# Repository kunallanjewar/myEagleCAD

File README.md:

# myEagleCAD

My EagleCAD circuit design for HAB IoT project.
Visit: https://sites.google.com/a/asu.edu/iot/

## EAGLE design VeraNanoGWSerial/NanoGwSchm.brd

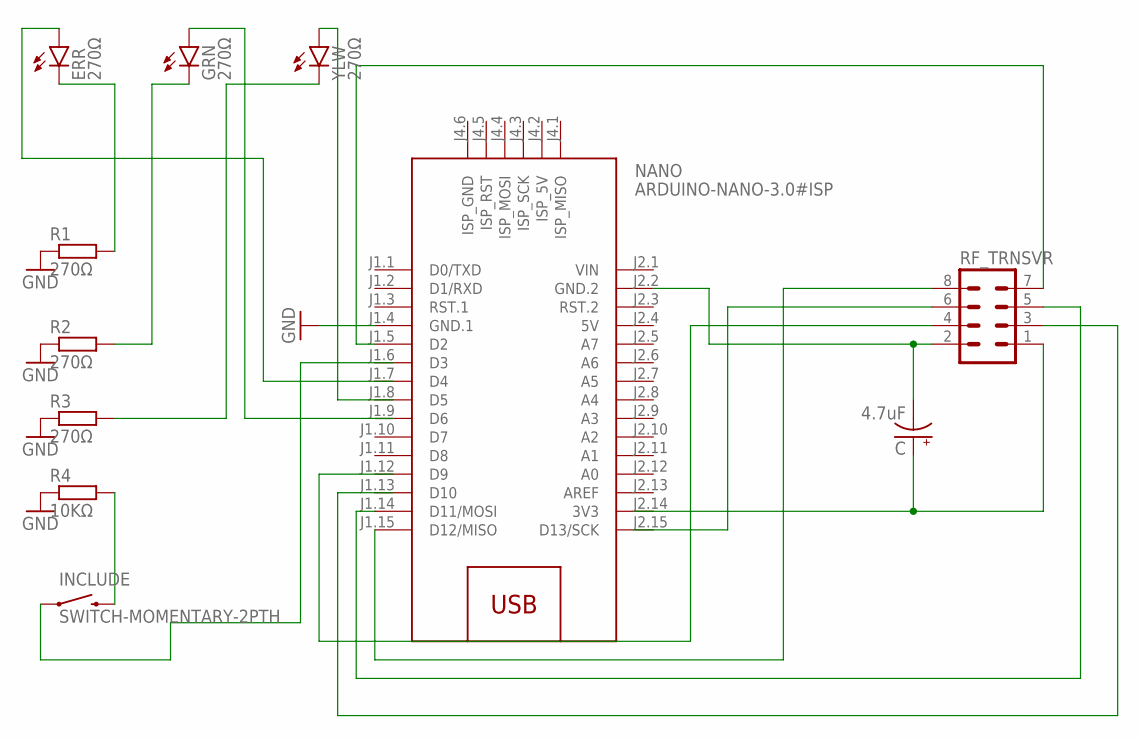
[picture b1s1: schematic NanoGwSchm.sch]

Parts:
C: 4.7uF; E2-5
ERR: 270Ω; LED5MM
GRN: 270Ω; LED5MM
INCLUDE: SWITCH-MOMENTARY-2PTH; TACTILE-PTH
NANO: ARDUINO-NANO-3.0#ISP
R1, R2, R3: 270Ω; 0204/7
R4: 10KΩ; 0204/7
RF_TRNSVR: MA04-2
YLW: 270Ω; LED5MM

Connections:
3V3: NANO.J2.14 (3V3)
5V: NANO.J2.4 (5V)
GND: NANO.J1.4 (GND.1), R1.1, R2.1, R3.1, R4.1
unnamed: ERR.K (C), R1.2
unnamed: GRN.K (C), R2.2
unnamed: R3.2, YLW.K (C)
unnamed: INCLUDE.3 (2), R4.2
unnamed: C.-, NANO.J2.2 (GND.2), RF_TRNSVR.2
unnamed: NANO.J1.14 (D11/MOSI), RF_TRNSVR.5
unnamed: NANO.J1.5 (D2), RF_TRNSVR.7
unnamed: NANO.J1.15 (D12/MISO), RF_TRNSVR.8
unnamed: C.+, RF_TRNSVR.1
VIN: NANO.J2.1 (VIN)

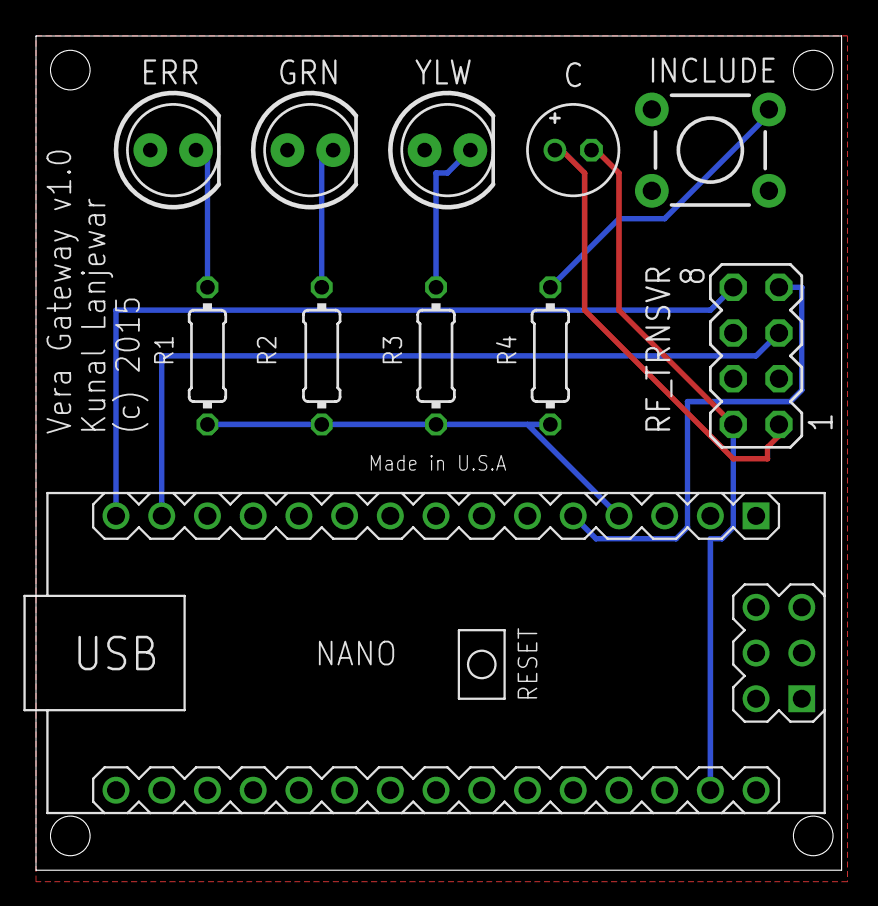
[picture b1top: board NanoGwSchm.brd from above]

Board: 2 copper layers, 44.8 x 46.3 mm, 11 parts (0 on the bottom side), 10 nets.

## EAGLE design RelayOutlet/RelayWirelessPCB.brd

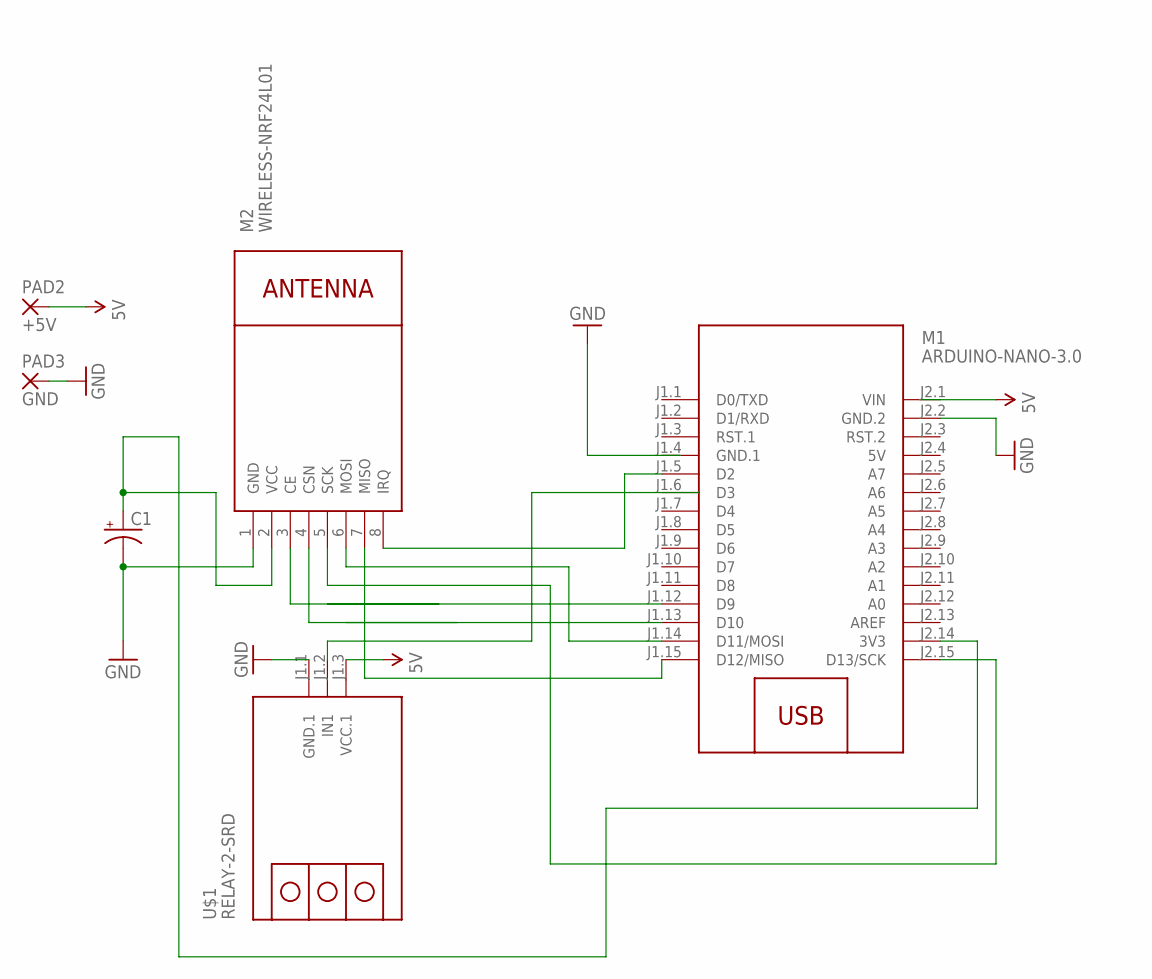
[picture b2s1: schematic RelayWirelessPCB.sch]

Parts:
C1: CPOL-USE3.5-8; E3,5-8
M1: ARDUINO-NANO-3.0
M2: WIRELESS-NRF24L01
PAD2: +5V; 4,16O1,6
PAD3: GND; 4,16O1,6
U$1: RELAY-2-SRD

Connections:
5V: M1.J2.1 (VIN), M1.J2.4 (5V), PAD2.1, U$1.J1.3 (VCC.1)
GND: C1.-, M1.J2.2 (GND.2), M2.1 (GND), PAD3.1, U$1.J1.1 (GND.1)
GND.1: M1.J1.4 (GND.1)
unnamed: M1.J1.12 (D9), M2.3 (CE)
unnamed: M1.J1.13 (D10), M2.4 (CSN)
unnamed: M1.J2.15 (D13/SCK), M2.5 (SCK)
unnamed: M1.J1.14 (D11/MOSI), M2.6 (MOSI)
unnamed: C1.+, M1.J2.14 (3V3), M2.2 (VCC)
unnamed: M1.J1.15 (D12/MISO), M2.7 (MISO)
unnamed: M1.J1.5 (D2), M2.8 (IRQ)

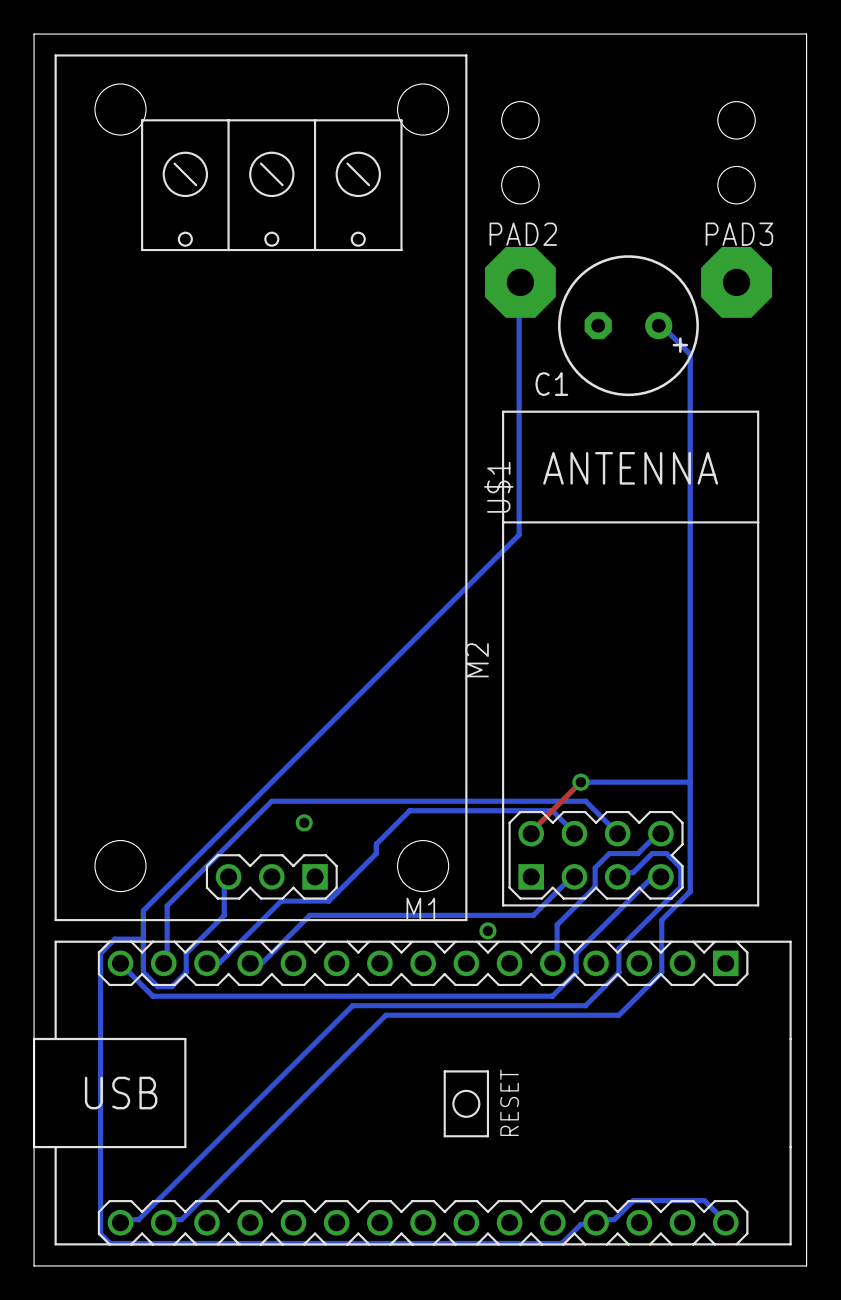
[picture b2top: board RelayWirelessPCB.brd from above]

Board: 2 copper layers, 45.4 x 72.4 mm, 6 parts (0 on the bottom side), 9 nets.

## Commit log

2015-10-01 Initial
2015-10-05 Add a Bitdeli badge to README

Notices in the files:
VeraNanoGWSerial/NanoGwSchm.brd:
(c) 2015
parts and their libraries:
diy-modules 3: Released under the Creative Commons Attribution 4.0 International License: http://creativecommons.org/licenses/by/4.0
SparkFun-Aesthetics: Licensing: Creative Commons ShareAlike 4.0 International - https://creativecommons.org/licenses/by-sa/4.0
